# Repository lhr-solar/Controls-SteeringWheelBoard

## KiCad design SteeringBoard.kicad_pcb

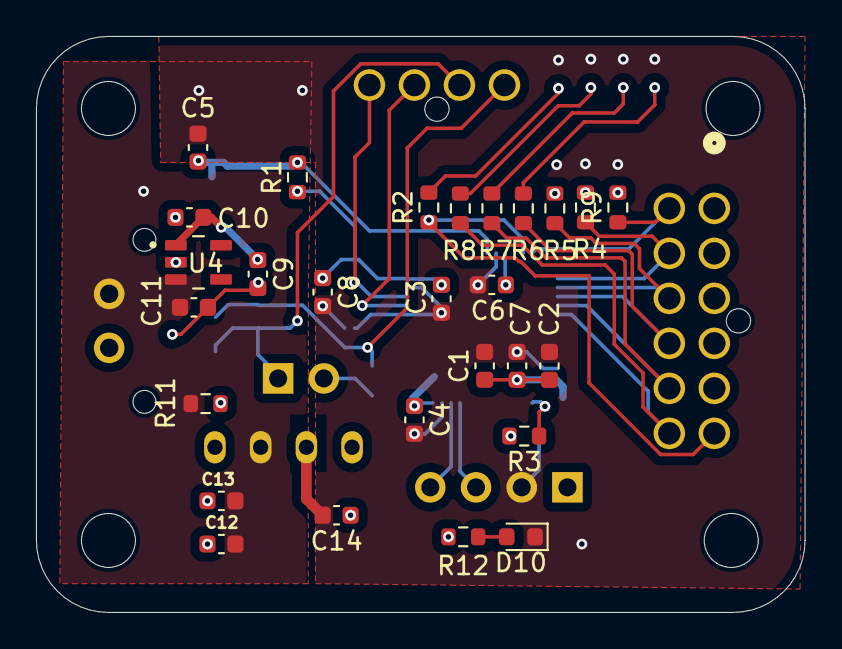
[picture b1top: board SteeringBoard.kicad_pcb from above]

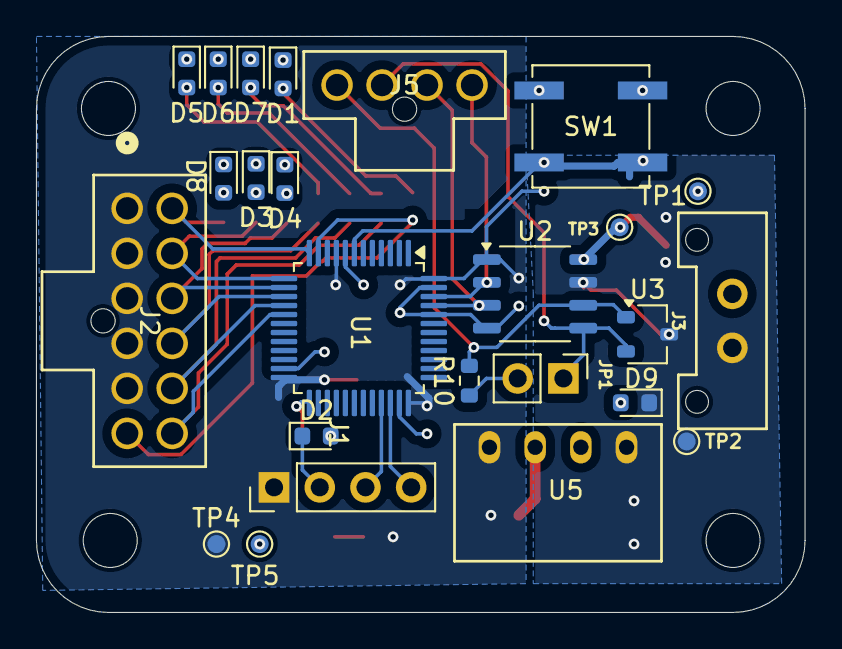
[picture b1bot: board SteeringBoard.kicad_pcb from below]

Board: 2 copper layers, 42.7 x 32.0 mm, 56 parts (25 on the bottom side), 31 nets.

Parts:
C1: 4.7uF; C_0603_1608Metric
C2, C3, C4, C5, C6, C7, C8, C9, C11: 100nF; C_0603_1608Metric
C10: 1nF; C_0603_1608Metric
C12, C13, C14: 10uF; C_0603_1608Metric
D1, D3, D4, D5, D6, D7, D8: LED; LED_0603_1608Metric
D2: Heartbeat; LED_0603_1608Metric
D9: 12V; LED_0603_1608Metric
D10: 3.3V; LED_0603_1608Metric
J1: SWD; PinHeader_1x04_P2.54mm_Vertical
J2: Conn_02x06_Counter_Clockwise; CONN_SD-105310-100_12_MOL
J3: Conn_01x02_Pin; Molex_MicroFit3.0_1x2xP3.00mm_PolarizingPeg_Vertical
J5: Conn_01x04_Pin; CONN_SD-105309-100_04_MOL
JP1: Termination Resistors; PinHeader_1x02_P2.54mm_Vertical
MH1, MH2, MH3, MH4: M.3; MountingHole_3mm
R1: 10K; R_0603_1608Metric
R2, R4, R5, R6, R7, R8, R9: R_US; R_0603_1608Metric
R3, R12: 2.2k; R_0603_1608Metric
R10: 120; R_0603_1608Metric
R11: 22.1k; R_0603_1608Metric
SW1: Reset; SW_SPST_B3SL-1002P
TP1, TP2, TP3, TP4, TP5: TestPoint; TestPoint_Pad_D1.0mm
U1: STM32L431CBTx; LQFP-48_7x7mm_P0.5mm
U2: ISO1044BD; SSOP-8_3.9x5.05mm_P1.27mm
U3: CDSOT23-T24CAN; SOT-23W
U4: TLV70130DBVR; SOT95P280X145-5N
U5: RO-123.3S; RI3_DC_Converter

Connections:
+3.3V: C1.1, C2.1, C3.1, C4.1, C6.1, C7.1, C8.1, C14.1, J1.1, J2.1, J2.2, J2.3, J2.4, J2.5, R1.1, R12.1, TP4.1, U1.9 (VDDA), U1.24 (VDD), U1.36 (VDD), U1.48 (VDD), U2.1 (VCC1), U5.4 (+Vout)
+12V: C11.1, C12.1, C13.1, J3.2, R11.1, TP1.1, U4.3 (IN), U5.2 (+Vin)
/3V3_Bus: C9.1, C10.1, TP3.1, U2.8 (VCC2), U4.1 (OUT)
/CAN/TERM_H: JP1.2 (B), R10.1
/CAN_H: J5.1, R10.2, U2.6 (CANH), U3.1 (CAN_H)
/CAN_L: J5.2, JP1.1 (A), U2.5 (CANL), U3.2 (CAN_L)
/CAN_RX: J5.3, U1.45 (PB8), U2.3 (RXD)
/CAN_TX: J5.4, U1.46 (PB9), U2.2 (TXD)
/CEN-: J2.10, R6.1, U1.15 (PA5)
/CRS_SET-: J2.9, R5.1, U1.14 (PA4)
/HRN_PD-: J2.12, R8.1, U1.17 (PA7)
/NRST: C5.1, R1.2, SW1.1, U1.7 (NRST)
/PA0: R3.1, U1.25 (PB12)
/RGEN_E-: J2.8, R4.1, U1.13 (PA3)
/SWCLK: J1.4, U1.34 (PA13)
/SWDIO: J1.3, U1.33 (PA12)
/TSSL-: J2.11, R7.1, U1.16 (PA6)
/TSSO-: J2.7, R9.1, U1.12 (PA2)
/TSSR-: J2.6, R2.1, U1.11 (PA1)
GND: C1.2, C2.2, C3.2, C4.2, C5.2, C6.2, C7.2, C8.2, C14.2, D1.1 (K), D2.1 (K), D3.1 (K), D4.1 (K), D5.1 (K), D6.1 (K), D7.1 (K), D8.1 (K), D10.1 (K), J1.2, SW1.2, TP5.1, U1.8 (VSSA), U1.23 (VSS), U1.35 (VSS), U1.44 (PH3), U1.47 (VSS), U2.4 (GND1), U5.3 (-Vout)
GNDPWR: C9.2, C10.2, C11.2, C12.2, C13.2, D9.1 (K), J3.1, TP2.1, U2.7 (GND2), U3.3 (GND), U4.2 (GND), U5.1 (-Vin)
unnamed: D1.2 (A), R2.2
unnamed: D2.2 (A), R3.2
unnamed: D3.2 (A), R4.2
unnamed: D4.2 (A), R5.2
unnamed: D5.2 (A), R6.2
unnamed: D6.2 (A), R7.2
unnamed: D7.2 (A), R8.2
unnamed: D8.2 (A), R9.2
unnamed: D9.2 (A), R11.2
unnamed: D10.2 (A), R12.2

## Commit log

2025-02-01 init commit
2025-02-01 scheme update
2025-02-15 layout changes
2025-02-15 Finished layout
2025-02-22 board update
2025-03-08 finished board with ldo
2025-03-08 finished board with bad edgecuts
2025-03-29 final
2025-04-12 fixed the switch
